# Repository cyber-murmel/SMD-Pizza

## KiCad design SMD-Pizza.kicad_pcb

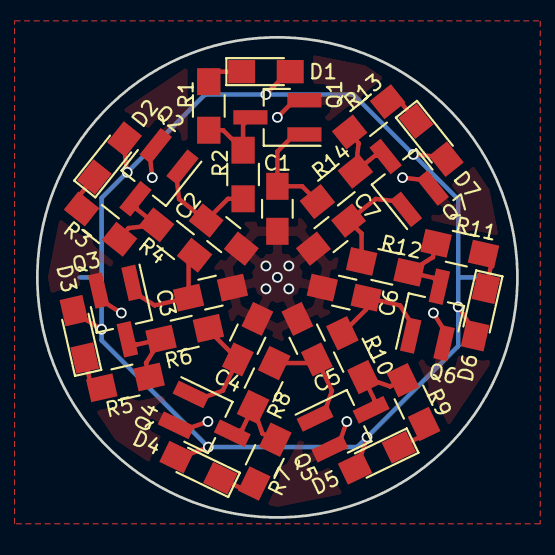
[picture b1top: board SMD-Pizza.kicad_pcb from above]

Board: 2 copper layers, 26.7 x 26.7 mm, 36 parts (1 on the bottom side), 23 nets.

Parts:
BT1: Battery_Cell; Keystone_3034_1x20mm-CoinCell
C1, C2, C3, C4, C5, C6, C7: 1u; C_0805_HandSoldering
D1, D2, D3, D4, D5, D6, D7: LED; LED_0805_HandSoldering
Q1, Q2, Q3, Q4, Q5, Q6, Q7: AO3400; SOT-23_Handsoldering
R1, R3, R5, R7, R9, R11, R13: 100; R_0805_HandSoldering
R2, R4, R6, R8, R10, R12, R14: 1M; R_0805_HandSoldering

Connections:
+BATT: BT1.1, D1.2, D2.2, D3.2, D4.2, D5.2, D6.2, D7.2
GND: BT1.2, C1.2, C2.2, C3.2, C4.2, C5.2, C6.2, C7.2, Q1.2, Q2.2, Q3.2, Q4.2, Q5.2, Q6.2, Q7.2
unnamed: C1.1, Q1.1, R14.1
unnamed: C2.1, Q2.1, R2.1
unnamed: C3.1, Q3.1, R4.1
unnamed: C4.1, Q4.1, R6.1
unnamed: C5.1, Q5.1, R8.1
unnamed: C6.1, Q6.1, R10.1
unnamed: C7.1, Q7.1, R12.1
unnamed: D1.1, R1.1
unnamed: D2.1, R3.1
unnamed: D3.1, R5.1
unnamed: D4.1, R7.1
unnamed: D5.1, R9.1
unnamed: D6.1, R11.1
unnamed: D7.1, R13.1
unnamed: Q1.3, R1.2, R2.2
unnamed: Q2.3, R3.2, R4.2
unnamed: Q3.3, R5.2, R6.2
unnamed: Q4.3, R7.2, R8.2
unnamed: Q5.3, R9.2, R10.2
unnamed: Q6.3, R11.2, R12.2
unnamed: Q7.3, R13.2, R14.2

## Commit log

2018-02-06 added schematic
2018-02-06 added pcb
2018-02-27 added solder maks for better battery contact
